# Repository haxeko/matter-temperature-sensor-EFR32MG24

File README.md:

# Cảm biến nhiệt độ/độ ẩm Matter-over-Thread — EFR32MG24 + CR2450

Thiết kế sơ bộ (v0.1) cho một cảm biến nhiệt độ và độ ẩm chạy 1 pin CR2450:
- Matter 1.6 over Thread, thiết bị ICD ngủ, commissioning qua BLE.
- Bo tròn Ø35 mm, nạp qua Tag-Connect TC2030.

> **Trạng thái:** đã có kiến trúc, tài liệu thiết kế và **project KiCad**: schematic hoàn chỉnh, PCB đã đặt linh kiện, **chưa đi dây**. **BOM chưa chốt** — xem [Câu hỏi mở](#câu-hỏi-mở-cần-trả-lời-trước-khi-chốt-bom).
> Dữ liệu tra cứu ngày 07/11/2026; bố cục PCB cập nhật 10/11/2026 (anten đồng trên PCB, cảm biến ở mép dưới, nút TS-1088, chữ in mặt sau).
> Nhãn trong tài liệu: **[SPEC]** bắt buộc theo spec · **[SDK]** đã đối chiếu mã nguồn · **[KN]** khuyến nghị · **[TT]** kinh nghiệm thực tế · **[ĐOÁN]** suy đoán.

## Quyết định chính

| Hạng mục | Chọn | Lý do ngắn |
|---|---|---|
| Spec | **Matter 1.6.x** (1.6 ra 17/06/2026, 1.6.1 ra 09/2026). 1.5 không còn mới nhất | ICD không đổi từ 1.4 nên thiết kế vẫn đúng với 1.5 |
| SoC | **EFR32MG24B010F1536IM40** (chip trần, QFN40, Vault High, +10 dBm) | Bo nhỏ + pin kim loại: chỉ chip trần cho phép dò anten theo bo, pin và vỏ. MGM240P quá lớn; anten loop của MGM240S hợp bo 55×30 mm |
| Cảm biến | **Sensirion SHT40-AD1B** (đo cả RH) | ±0,2 °C typ / ±1,8 %RH, 2,2 µC mỗi lần đo, chạy từ 1,08 V. SHT45 nếu cần ±0,1 °C |
| Vai trò Thread | **SED**, ICD **LIT-capable, tự fallback SIT**. **Không dùng SSED** | CSL bị giới hạn khoảng 10,5 s và = poll interval, nên tốn hơn (14 µA so với 5 µA) |
| ICD | Idle 1800 s · ActiveModeDuration 0 · Threshold 5 s · poll 15 s (SIT) / 30 phút (LIT) · fast 500 ms · ShortIdle = Idle | Tránh "bẫy" ShortIdle 60 s (+5,7 µA) |
| Báo cáo | Đo 30 s; vùng chết 0,2 °C / 2 %RH (mềm 0,1 / 1, đi kèm lần thức kế tiếp); đồng bộ subscription; report-on-active | Không thức radio thêm |
| Nguồn | P-MOSFET DMP2035U (chống ngược) + 2×100 µF + DC-DC nội; TX +8 dBm, +4 dBm khi pin yếu/lạnh | CR2450 không chịu +10 dBm cố định ở cuối đời/lạnh |
| Đo pin | IADC đo AVDD/4 nội (không cầu chia) + thuật toán lai: đếm điện tích + áp | Rò = 0; % pin không "đứng 100 % rồi rơi" |
| OTA | Bật; lưu trong flash nội (GBL nén LZMA) | Không cần SPI flash; EM2 thấp hơn |
| Anten | **IFA đồng trên PCB** (chép TI AN043, 15,2 × 5,7 mm) ở mép trên + mạng π tinh chỉnh | Không tốn linh kiện, không lo tồn kho; vừa dải 7,25 mm không pin. **Phải tinh chỉnh bằng VNA** (mục 4.5) |
| PCB | Ø35 mm, 4 lớp 0,8 mm ENIG; pin lệch tâm 2,0 mm; anten ở 12 giờ; lưỡi cảm biến 2 khe ở **6 giờ** (SHT40 ở mép dưới); TC2030 ở 10 giờ; nút SMD 3,9 × 3 mm 2 chân (TS-1088) | Thân kẹp MY-2450-03 không cho lệch tâm hơn 2 mm (mục 4.11) |
| Năng lượng | Mô hình khoảng **5,1 µA** (SIT) / 3,9 µA (LIT). **Cho phép ≤ 20,8 µA** cho 18 tháng (thận trọng) | Biên gấp khoảng 4 lần. Rủi ro nằm ở cấu hình firmware, không ở phần cứng |

## Tài liệu (đi theo đúng thứ tự yêu cầu)

| # | Tài liệu | Nội dung |
|---|---|---|
| 1 | [docs/01-soc-and-architecture.md](docs/01-soc-and-architecture.md) | Yêu cầu, giả định; **chip trần vs MGM240S/P**; **các mâu thuẫn và phương án**; kiến trúc |
| 2 | [docs/02-matter-compliance.md](docs/02-matter-compliance.md) | Phiên bản spec; endpoint/cluster; Power Source; ICD SIT/LIT, Check-In, UAT, tham số; **hệ sinh thái nào hỗ trợ LIT**; subscription/đồng bộ; commissioning; DAC/PAI/PAA/CD; DIY vs thương mại; OTA |
| 3 | [docs/03-commercial-benchmark.md](docs/03-commercial-benchmark.md) | Eve Weather, Aqara W100, Onvis, IKEA TIMMERFLOTTE (**MG24 + SHT4x**), Aqara T1; phân rõ chính thức / cộng đồng / suy đoán |
| 4 | [docs/04-hardware.md](docs/04-hardware.md) | So sánh cảm biến; nguồn CR2450 và sụt áp; chống ngược; đo pin; RF/anten; thạch anh; layout; gán chân; BOM |
| 5 | [docs/05-firmware.md](docs/05-firmware.md) | Ví dụ gốc; luồng EM2→đo→ngưỡng→báo cáo; nút/LED; đo pin; chính sách ICD đa fabric; mất parent; thay pin; component; cấu hình ICD; provisioning |
| 6 | [docs/06-power-budget.md](docs/06-power-budget.md) | Bảng điện tích từng sự kiện, 7 kịch bản, hệ số an toàn, **3 thông số ảnh hưởng nhất**, quy trình đo Energy Profiler/PPK2 |
| 7 | [docs/07-test-plan.md](docs/07-test-plan.md) | Kế hoạch kiểm thử: bring-up, Matter, RF, dòng, độ chính xác, hệ sinh thái; tiêu chí "đóng băng" thiết kế |

Tệp đi kèm:
- [`hardware/kicad/`](hardware/kicad): **project KiCad** (mở bằng KiCad ≥ 7):
  - `tsensor.kicad_sch` (schematic A3);
  - `tsensor.kicad_pcb` (Ø35 mm 4 lớp, đã đặt linh kiện, zone, vùng cấm; **chưa đi dây**);
  - `lib/` (symbol EFR32MG24 QFN40, footprint QFN40 và kẹp pin);
  - `plots/` (PDF schematic, SVG PCB hai mặt);
  - `build/` (BOM JLCPCB, CPL, báo cáo DRC, netlist).
  - Chi tiết và việc cần làm khi đi dây: mục 4.11.
- [`hardware/bom.csv`](hardware/bom.csv): BOM nháp v0.1 có mã LCSC đã kiểm (07/11/2026). Biến thể A = chip trần, B = MGM240S.
- [`hardware/floorplan.svg`](hardware/floorplan.svg): bố trí theo tỉ lệ, khớp PCB v0.1 (anten, lưỡi cảm biến, TC2030, kẹp pin).
- [`tools/power_budget.py`](tools/power_budget.py): mô hình năng lượng có tham số, kịch bản và phân tích độ nhạy.
- [`tools/kicad_gen/`](tools/kicad_gen): bộ sinh project KiCad từ `design.py` (nguồn dữ liệu duy nhất cho linh kiện, net, vị trí), có kiểm tra netlist và DRC.
- [`firmware/app-logic/`](firmware/app-logic): logic firmware không phụ thuộc phần cứng, có test chạy trên host:
  - driver SHT4x (CRC, chuyển đổi);
  - chính sách báo cáo (vùng chết hai tầng);
  - ước tính pin (Power Source);
  - máy trạng thái nút.

```bash
python3 tools/power_budget.py --sensitivity            # ngân sách năng lượng
python3 tools/power_budget.py --markdown               # bảng Markdown
cmake -S firmware/app-logic -B build && cmake --build build && ctest --test-dir build   # 102 kiểm tra
tools/kicad_gen/build.sh   # sinh lại project KiCad + kiểm netlist + DRC (cần KiCad 7, GHI ĐÈ file KiCad)
```

## Câu hỏi mở (cần trả lời trước khi chốt BOM)

1. **Mục đích và số lượng**:
   - DIY (vài chiếc) hay bán thương mại?
   - Bao nhiêu chiếc/năm, bán ở thị trường nào (Việt Nam / Mỹ / EU)?

   Câu này quyết định chip trần hay MGM240S, và lộ trình chứng nhận (CSA, Thread, FCC/CE, hợp quy VN).
2. **Đo RF**: anh/chị có VNA (kể cả NanoVNA) hoặc tiếp cận được phòng đo RF không? Không có thì nên làm biến thể B (MGM240S) song song.
3. **Kích thước**:
   - Có chấp nhận **Ø35 mm** (Ø32 gần như không chứa được kẹp CR2450)?
   - Có được tăng lên **Ø38–40 mm** nếu thử RF (T3.5) không đạt?
4. **Môi trường dùng**:
   - Chỉ trong nhà?
   - Có phòng tắm/bếp (nên dùng SHT4x-AD1F có màng)?
   - Có nơi lạnh như garage/ngoài trời (CR2450 ở −10…−20 °C, cần vỏ IP)?
5. **Độ chính xác công bố**: ±0,2 °C (SHT40) hay ±0,1 °C (SHT45)? Có hiệu chuẩn offset cho từng chiếc không?
6. **Hệ sinh thái ưu tiên** (Apple / Google / Home Assistant / SmartThings). Có cần LIT ngay từ bản đầu, hay chấp nhận chỉ SIT để đơn giản?
7. **Lắp ráp**: JLCPCB PCBA 2 mặt (kẹp pin SMD ở mặt sau), hay hàn tay kẹp/bản THT?
8. **OTA** có cần ngay ở bản đầu (DIY có thể tạm tắt)?
9. **Vỏ**:
   - In 3D hay ép nhựa?
   - Đặt bàn hay dán tường?
   - Có nam châm hoặc tấm kim loại (ảnh hưởng anten) không?
10. **Ngân sách BOM** mục tiêu mỗi chiếc. Hiện ước tính khoảng 12,7 USD @100 ở LCSC, khoảng 8,5–9,5 USD @1k ở nhà phân phối chính hãng (anten là đồng trên PCB nên không tốn tiền).

## Những điểm phải xác minh trước khi đặt mạch

- Giá trị mạng phối hợp RF cho **QFN40** (AN930.2 / schematic tham chiếu). Số hiện tại lấy từ BRD4186C (QFN48).
- Tụ decoupling cho từng chân nguồn MG24: chép đúng schematic tham chiếu Silicon Labs.
- Chân SOT-23 của DMP2035U (G = 1, S = 2, D = 3) và chân thạch anh TZ3541C (1/3 = thạch anh, 2/4 = GND).
- Anten IFA chép từ TI AN043 nhưng đặt trên bo khác (mặt đất Ø35 mm, pin kim loại, vỏ): đo S11 (T3.1), chỉnh mạng π, nếu cần thì sửa chiều dài nhánh hở.
- SiSDK có tự chuyển DC-DC sang bypass khi VBAT < 2,2–2,3 V không.
- Đường cong áp→% của CR2450 trong `battery_estimator.h` là **giả định** và phải thay bằng số đo.

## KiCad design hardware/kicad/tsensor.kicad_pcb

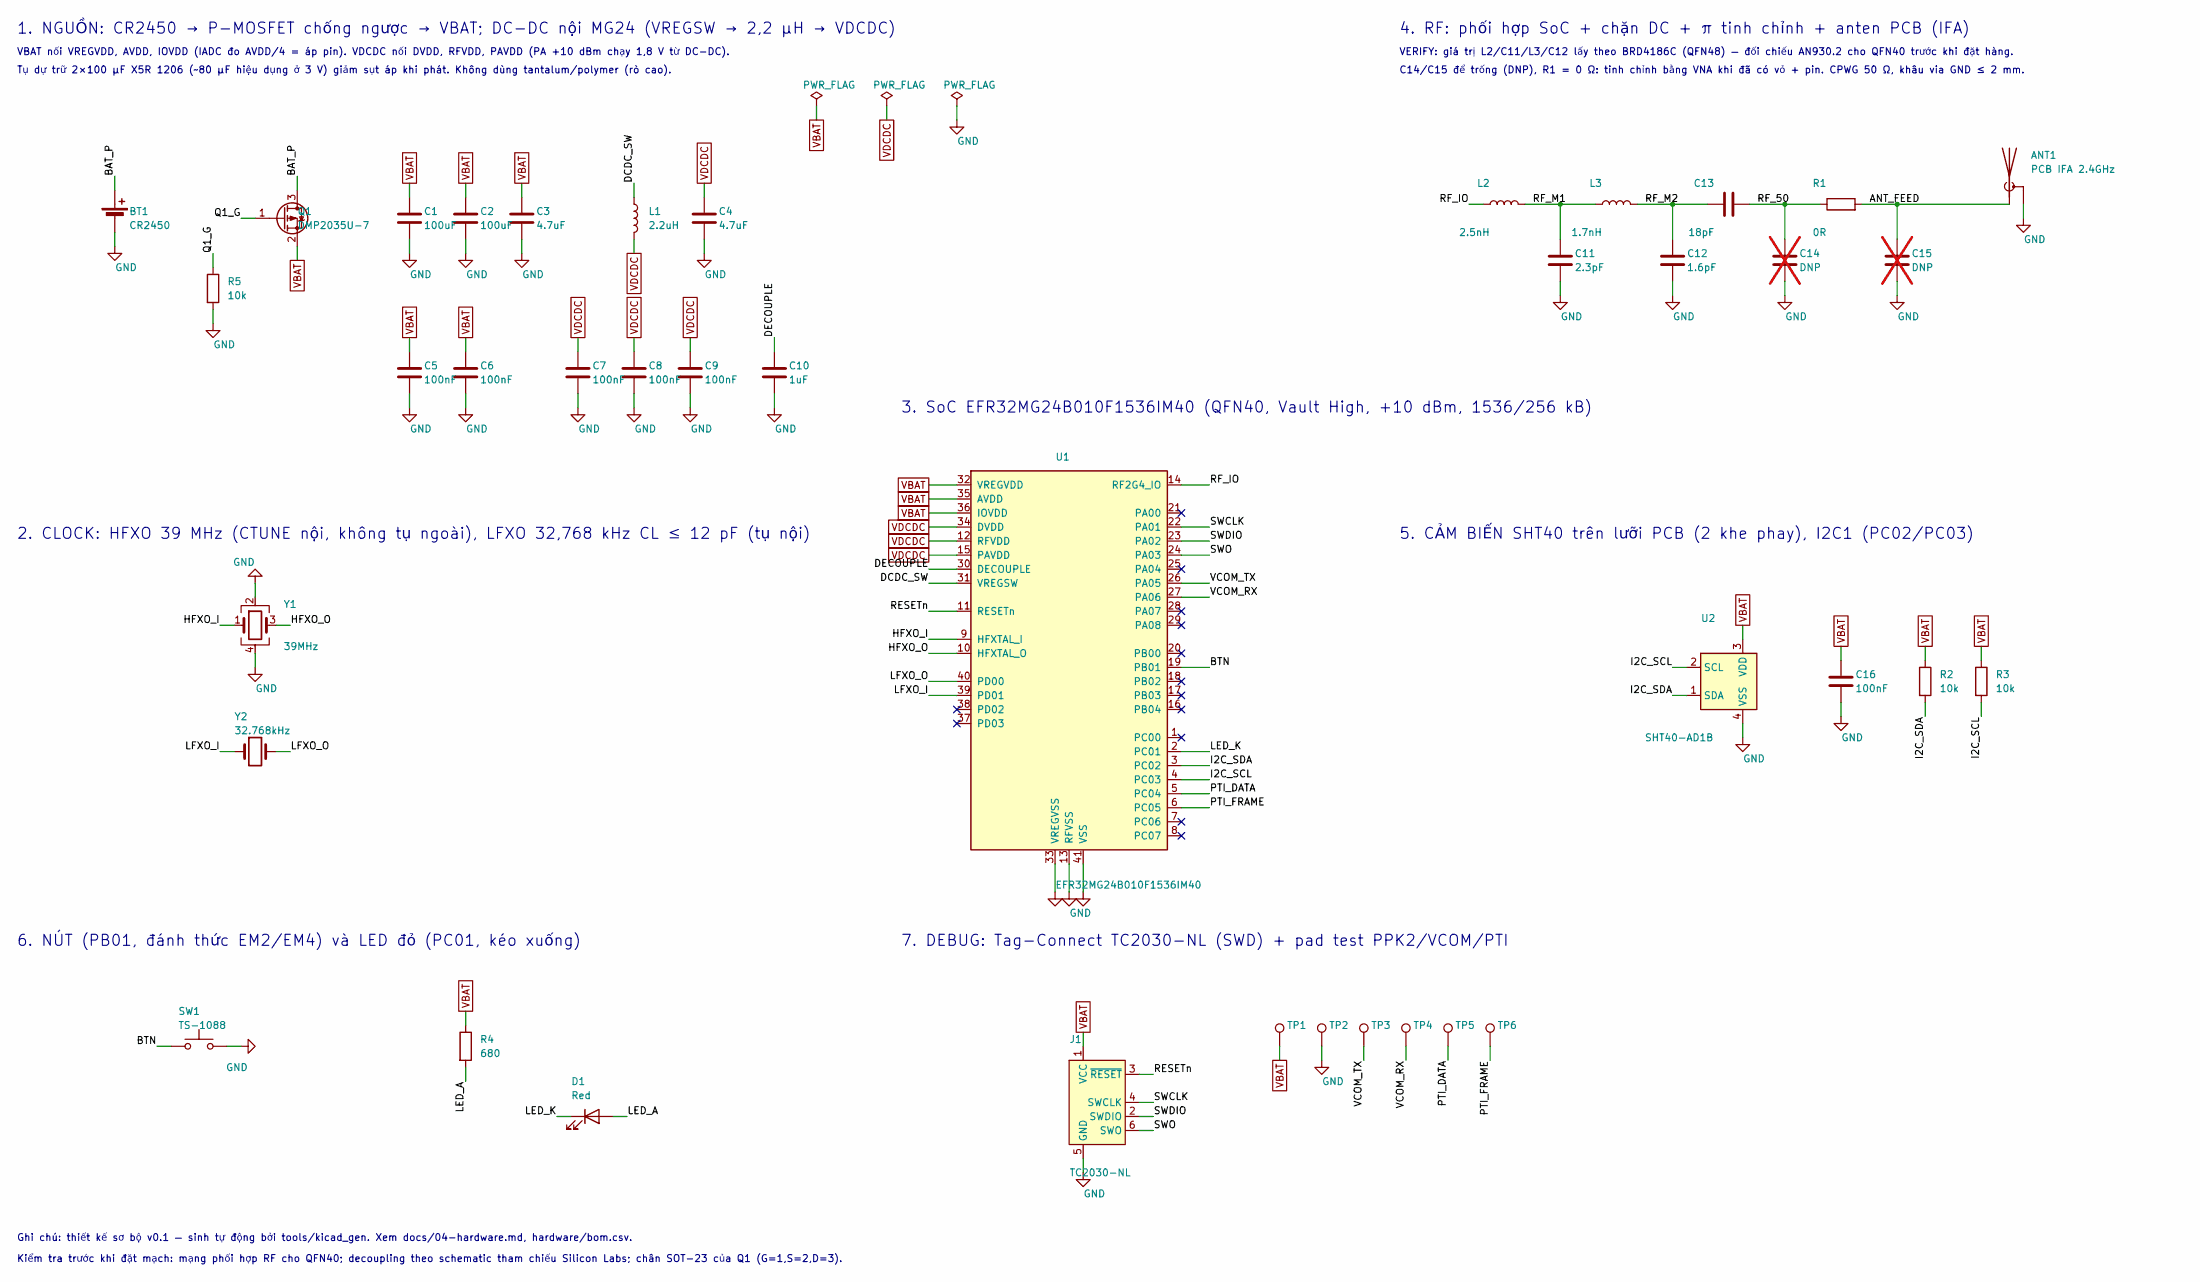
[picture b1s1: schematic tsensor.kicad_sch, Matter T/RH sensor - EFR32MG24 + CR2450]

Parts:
ANT1: PCB IFA 2.4GHz; PCB_Antenna_IFA_2G4_TI-AN043
BT1: CR2450; BatteryClip_MYOUNG_MY-2450-03_CR2450; MPN MY-2450-03; LCSC C2988622
C1, C2: 100uF; C_1206_3216Metric; MPN CL31A107MQHNNNE; LCSC C15008
C3, C4: 4.7uF; C_0603_1608Metric; MPN TCC0603X7R475K6R3CT; LCSC C5360855
C5, C6, C7, C8, C9, C16: 100nF; C_0402_1005Metric; MPN CL05B104KO5NNNC; LCSC C1525
C10: 1uF; C_0402_1005Metric; MPN CL05A105KA5NQNC; LCSC C52923
C11: 2.3pF; C_0201_0603Metric; MPN GRM0335C1H2R3WA01D; LCSC C710810
C12: 1.6pF; C_0201_0603Metric; MPN GRM0335C1H1R6WA01D; LCSC C1864525
C13: 18pF; C_0201_0603Metric; MPN GRM0335C1H180JA01D; LCSC C85892
C14, C15: DNP; C_0402_1005Metric; not fitted
D1: Red; LED_0603_1608Metric; MPN APTD1608LSURCK; LCSC C5342734
J1: TC2030-NL; Tag-Connect_TC2030-IDC-NL_2x03_P1.27mm_Vertical
L1: 2.2uH; L_1008_2520Metric; MPN DFE2HCAH2R2MJ0L; LCSC C2043106
L2: 2.5nH; L_0201_0603Metric; MPN LQP03HQ2N5B02D; LCSC C237441
L3: 1.7nH; L_0201_0603Metric; MPN LQP03HQ1N7B02D; LCSC C2041495
Q1: DMP2035U-7; SOT-23; MPN DMP2035U-7; LCSC C110499
R1: 0R; R_0402_1005Metric; MPN 0402WGF0000TCE; LCSC C17168
R2, R3, R5: 10k; R_0402_1005Metric; MPN 0402WGF1002TCE; LCSC C25744
R4: 680; R_0402_1005Metric; MPN 0402WGF6800TCE; LCSC C25130
SW1: TS-1088; SW_SPST_XUNPU_TS-1088_3.9x3mm; MPN TS-1088-AR02016; LCSC C720477
TP1: VBAT; TestPoint_Pad_D1.0mm
TP2: GND; TestPoint_Pad_D1.0mm
TP3: VCOM_TX; TestPoint_Pad_D1.0mm
TP4: VCOM_RX; TestPoint_Pad_D1.0mm
TP5: PTI_DATA; TestPoint_Pad_D1.0mm
TP6: PTI_FRAME; TestPoint_Pad_D1.0mm
U1: EFR32MG24B010F1536IM40; EFR32MG24_QFN40_5x5mm_P0.4mm_EP3.85x3.85mm; MPN EFR32MG24B010F1536IM40-B; LCSC C6033375
U2: SHT40-AD1B; Sensirion_DFN-4_1.5x1.5mm_P0.8mm_SHT4x_NoCentralPad; MPN SHT40-AD1B-R3; LCSC C2848306
Y1: 39MHz; Crystal_SMD_2016-4Pin_2.0x1.6mm; MPN TZ3541C; LCSC C5360883
Y2: 32.768kHz; Crystal_SMD_2012-2Pin_2.0x1.2mm; MPN FC-12M 32.768kHz 9pF; LCSC C96341

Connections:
/ANT_FEED: ANT1.1 (A), C15.1, R1.2
/BAT_P: BT1.1 (+), Q1.3 (D)
/BTN: SW1.1, U1.19 (PB01)
/DCDC_SW: L1.1, U1.31 (VREGSW)
/DECOUPLE: C10.1, U1.30 (DECOUPLE)
/HFXO_I: U1.9 (HFXTAL_I), Y1.1
/HFXO_O: U1.10 (HFXTAL_O), Y1.3
/I2C_SCL: R3.2, U1.4 (PC03), U2.2 (SCL)
/I2C_SDA: R2.2, U1.3 (PC02), U2.1 (SDA)
/LED_A: D1.2 (A), R4.2
/LED_K: D1.1 (K), U1.2 (PC01)
/LFXO_I: U1.39 (PD01), Y2.1
/LFXO_O: U1.40 (PD00), Y2.2
/PTI_DATA: TP5.1, U1.5 (PC04)
/PTI_FRAME: TP6.1, U1.6 (PC05)
/Q1_G: Q1.1 (G), R5.1
/RESETn: J1.3 (~RESET), U1.11 (RESETn)
/RF_50: C13.2, C14.1, R1.1
/RF_IO: L2.1, U1.14 (RF2G4_IO)
/RF_M1: C11.1, L2.2, L3.1
/RF_M2: C12.1, C13.1, L3.2
/SWCLK: J1.4 (SWCLK), U1.22 (PA01)
/SWDIO: J1.2 (SWDIO), U1.23 (PA02)
/SWO: J1.6 (SWO), U1.24 (PA03)
/VCOM_RX: TP4.1, U1.27 (PA06)
/VCOM_TX: TP3.1, U1.26 (PA05)
GND: ANT1.2 (Shield), BT1.2 (-), C1.2, C2.2, C3.2, C4.2, C5.2, C6.2, C7.2, C8.2, C9.2, C10.2, C11.2, C12.2, C14.2, C15.2, C16.2, J1.5 (GND), R5.2, SW1.2, TP2.1, U1.13 (RFVSS), U1.33 (VREGVSS), U1.41 (VSS), U2.4 (VSS), Y1.2, Y1.4
VBAT: C1.1, C2.1, C3.1, C5.1, C6.1, C16.1, J1.1 (VCC), Q1.2 (S), R2.1, R3.1, R4.1, TP1.1, U1.32 (VREGVDD), U1.35 (AVDD), U1.36 (IOVDD), U2.3 (VDD)
VDCDC: C4.1, C7.1, C8.1, C9.1, L1.2, U1.12 (RFVDD), U1.15 (PAVDD), U1.34 (DVDD)

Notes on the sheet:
1. NGUỒN: CR2450 → P-MOSFET chống ngược → VBAT; DC-DC nội MG24 (VREGSW → 2,2 µH → VDCDC)
VBAT nối VREGVDD, AVDD, IOVDD (IADC đo AVDD/4 = áp pin). VDCDC nối DVDD, RFVDD, PAVDD (PA +10 dBm chạy 1,8 V từ DC-DC).
Tụ dự trữ 2×100 µF X5R 1206 (~80 µF hiệu dụng ở 3 V) giảm sụt áp khi phát. Không dùng tantalum/polymer (rò cao).
2. CLOCK: HFXO 39 MHz (CTUNE nội, không tụ ngoài), LFXO 32,768 kHz CL ≤ 12 pF (tụ nội)
3. SoC EFR32MG24B010F1536IM40 (QFN40, Vault High, +10 dBm, 1536/256 kB)
4. RF: phối hợp SoC + chặn DC + π tinh chỉnh + anten PCB (IFA)
VERIFY: giá trị L2/C11/L3/C12 lấy theo BRD4186C (QFN48) — đối chiếu AN930.2 cho QFN40 trước khi đặt hàng.
C14/C15 để trống (DNP), R1 = 0 Ω: tinh chỉnh bằng VNA khi đã có vỏ + pin. CPWG 50 Ω, khâu via GND ≤ 2 mm.
5. CẢM BIẾN SHT40 trên lưỡi PCB (2 khe phay), I2C1 (PC02/PC03)
6. NÚT (PB01, đánh thức EM2/EM4) và LED đỏ (PC01, kéo xuống)
7. DEBUG: Tag-Connect TC2030-NL (SWD) + pad test PPK2/VCOM/PTI
Ghi chú: thiết kế sơ bộ v0.1 — sinh tự động bởi tools/kicad_gen. Xem docs/04-hardware.md, hardware/bom.csv.
Kiểm tra trước khi đặt mạch: mạng phối hợp RF cho QFN40; decoupling theo schematic tham chiếu Silicon Labs; chân SOT-23 của Q1 (G=1,S=2,D=3).

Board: 4 copper layers, 40 parts (1 on the bottom side), 29 nets, no tracks yet.

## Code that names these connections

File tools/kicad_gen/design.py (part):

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# ---------------------------------------------------------------------------
MG24_PINS = {
    1: ("PC00", "bidirectional", NC),
    2: ("PC01", "bidirectional", "LED_K"),
    3: ("PC02", "bidirectional", "I2C_SDA"),
    4: ("PC03", "bidirectional", "I2C_SCL"),
    5: ("PC04", "bidirectional", "PTI_DATA"),
    6: ("PC05", "bidirectional", "PTI_FRAME"),
    7: ("PC06", "bidirectional", NC),
    8: ("PC07", "bidirectional", NC),
    9: ("HFXTAL_I", "input", "HFXO_I"),
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    16: ("PB04", "bidirectional", NC),
    17: ("PB03", "bidirectional", NC),
    18: ("PB02", "bidirectional", NC),
    19: ("PB01", "bidirectional", "BTN"),        # EM2 wake (cổng B), EM4WU3
    20: ("PB00", "bidirectional", NC),
    21: ("PA00", "bidirectional", NC),
    22: ("PA01", "bidirectional", "SWCLK"),
    23: ("PA02", "bidirectional", "SWDIO"),
    24: ("PA03", "bidirectional", "SWO"),
    25: ("PA04", "bidirectional", NC),
    26: ("PA05", "bidirectional", "VCOM_TX"),
    27: ("PA06", "bidirectional", "VCOM_RX"),
    28: ("PA07", "bidirectional", NC),
    29: ("PA08", "bidirectional", NC),
    30: ("DECOUPLE", "power_out", "DECOUPLE"),
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    36: ("IOVDD", "power_in", "VBAT"),
    37: ("PD03", "bidirectional", NC),
    38: ("PD02", "bidirectional", NC),
    39: ("PD01", "bidirectional", "LFXO_I"),     # LFXTAL_I
    40: ("PD00", "bidirectional", "LFXO_O"),     # LFXTAL_O
    41: ("VSS", "power_in", "GND"),              # exposed pad
}

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# Khung chữ trên schematic: (x, y, cỡ chữ, nội dung)
SCH_TEXTS = [
    (20.32, 30.48, 2.0, "1. NGUỒN: CR2450 → P-MOSFET chống ngược → VBAT; DC-DC nội MG24 (VREGSW → 2,2 µH → VDCDC)"),
    (20.32, 34.29, 1.27, "VBAT nối VREGVDD, AVDD, IOVDD (IADC đo AVDD/4 = áp pin). VDCDC nối DVDD, RFVDD, PAVDD (PA +10 dBm chạy 1,8 V từ DC-DC)."),
    (20.32, 37.59, 1.27, "Tụ dự trữ 2×100 µF X5R 1206 (~80 µF hiệu dụng ở 3 V) giảm sụt áp khi phát. Không dùng tantalum/polymer (rò cao)."),
    (20.32, 121.92, 2.0, "2. CLOCK: HFXO 39 MHz (CTUNE nội, không tụ ngoài), LFXO 32,768 kHz CL ≤ 12 pF (tụ nội)"),
    (180.34, 99.06, 2.0, "3. SoC EFR32MG24B010F1536IM40 (QFN40, Vault High, +10 dBm, 1536/256 kB)"),
    (270.51, 30.48, 2.0, "4. RF: phối hợp SoC + chặn DC + π tinh chỉnh + anten PCB (IFA)"),
    (270.51, 34.29, 1.27, "VERIFY: giá trị L2/C11/L3/C12 lấy theo BRD4186C (QFN48) — đối chiếu AN930.2 cho QFN40 trước khi đặt hàng."),
    (270.51, 37.59, 1.27, "C14/C15 để trống (DNP), R1 = 0 Ω: tinh chỉnh bằng VNA khi đã có vỏ + pin. CPWG 50 Ω, khâu via GND ≤ 2 mm."),
    (270.51, 121.92, 2.0, "5. CẢM BIẾN SHT40 trên lưỡi PCB (2 khe phay), I2C1 (PC02/PC03)"),
    (20.32, 195.58, 2.0, "6. NÚT (PB01, đánh thức EM2/EM4) và LED đỏ (PC01, kéo xuống)"),
    (180.34, 195.58, 2.0, "7. DEBUG: Tag-Connect TC2030-NL (SWD) + pad test PPK2/VCOM/PTI"),
    (20.32, 248.92, 1.27, "Ghi chú: thiết kế sơ bộ v0.1 — sinh tự động bởi tools/kicad_gen. Xem docs/04-hardware.md, hardware/bom.csv."),
    (20.32, 252.73, 1.27, "Kiểm tra trước khi đặt mạch: mạng phối hợp RF cho QFN40; decoupling theo schematic tham chiếu Silicon Labs; chân SOT-23 của Q1 (G=1,S=2,D=3)."),
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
